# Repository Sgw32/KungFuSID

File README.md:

**Updater app is currently not working! Do not use it.**

# Kung Fu SID GD32 version

IMPORTANT! Firmware is adjusted for new Kung Fu SID hardware (and only)

## Introduction

Project is heavily inspired by __SwinSID__ and __ArmSID__ project. And is maintained as an open-source alternative to them.
Now it is even working on a GD32F405RGT6 on 168 MHz with 8 MHz crystal, just like Kung Fu Flash - and firmware is using critical code from KFF. 
I'm looking for contributers(I can even pay for the work) who will add some assembler optimization magic into SID code. 

A firmware for Kung Fu Flash and Kung Fu Flash GD32 which emulates SID via internal DAC of STM32F405RGT6
All hardware files are copied from "UltiSID" , projects are merged. 
Original UltiSID firmware is obsolete and current Kung Fu SID firmware just is partly based on it in IRQ and SID emulation. 

You can test Kung Fu SID by compiling firmware and flashing to your kung fu flash. 

To use it with original KungFuFlash cartridge output - check previous commits. 
Now only KungFuSID hardware is supported(and devices are selling)

Example usage with MixSIDs (you can use it directly, of course)

Patched by avrem for GD32F405RGT6 microcontroller.
Patch includes:
* ARR timer fix for GD32
* Memory remap fix (since KFF is running from RAM)

You can use both GD32 or STM32. 

## Future plans

I need to finish paddles, 6581-8580 switch and make a bootloader(optional, though). Probably, that's it and project will be finished. 
Some tunes still require some improvements, e.g. Artillery Credits by Geir Tjelta

## Limitations

* No 6581/8580 switch
* No paddles(can be done though)

## Video(and audio) 

## New video:

**PLEASE LIKE AND SUBSCRIBE😊**

Old video featuring old UltiSID firmware:

## Credits and special thanks:

* Tolaemon's NanoSwinSID page with open-hardware PCB available: http://www.tolaemon.com/nss/ 
My PCB is a modified version of SwinSID PCB

* ArmSID page with schematic: https://www.nobomi.cz/8bit/armsid/index_en.php
* Teensy SID emulator (huuuge, not really good): https://www.pjrc.com/c64-sid-chip-replacement/ and https://github.com/kokotisp/6581-SID-teensy
* SID BluePill emulators:
https://github.com/Bakisha/STM32-SID-PLAYER - my code is 80% based on this repository
https://github.com/dkm1978/BluePillSid - references
* Swinkels page - dead http://www.swinkels.tvtom.pl/swinsid/
Available on Archive.org - please check it, there is a SID emulation source for SwinSID atmega8515.
* Kung Fu Flash - https://github.com/KimJorgensen/KungFuFlash
I am inspired by simplicity of it and its power. 
* Pavel Myasnikov
Author of KungFuSID hardware design 
* Special greetings to Protovision Games

## Support us

Buy UltiSID here:
https://www.amibay.com/threads/kungfusid-sid-chip-emulator.2449119/

Crypto: 
0xeDc17cb23241eACe19DF3617291aa7d2d92E62DC (ETH, USDT ERC20)
Buy something here (3d models):
https://www.cgtrader.com/sgw32

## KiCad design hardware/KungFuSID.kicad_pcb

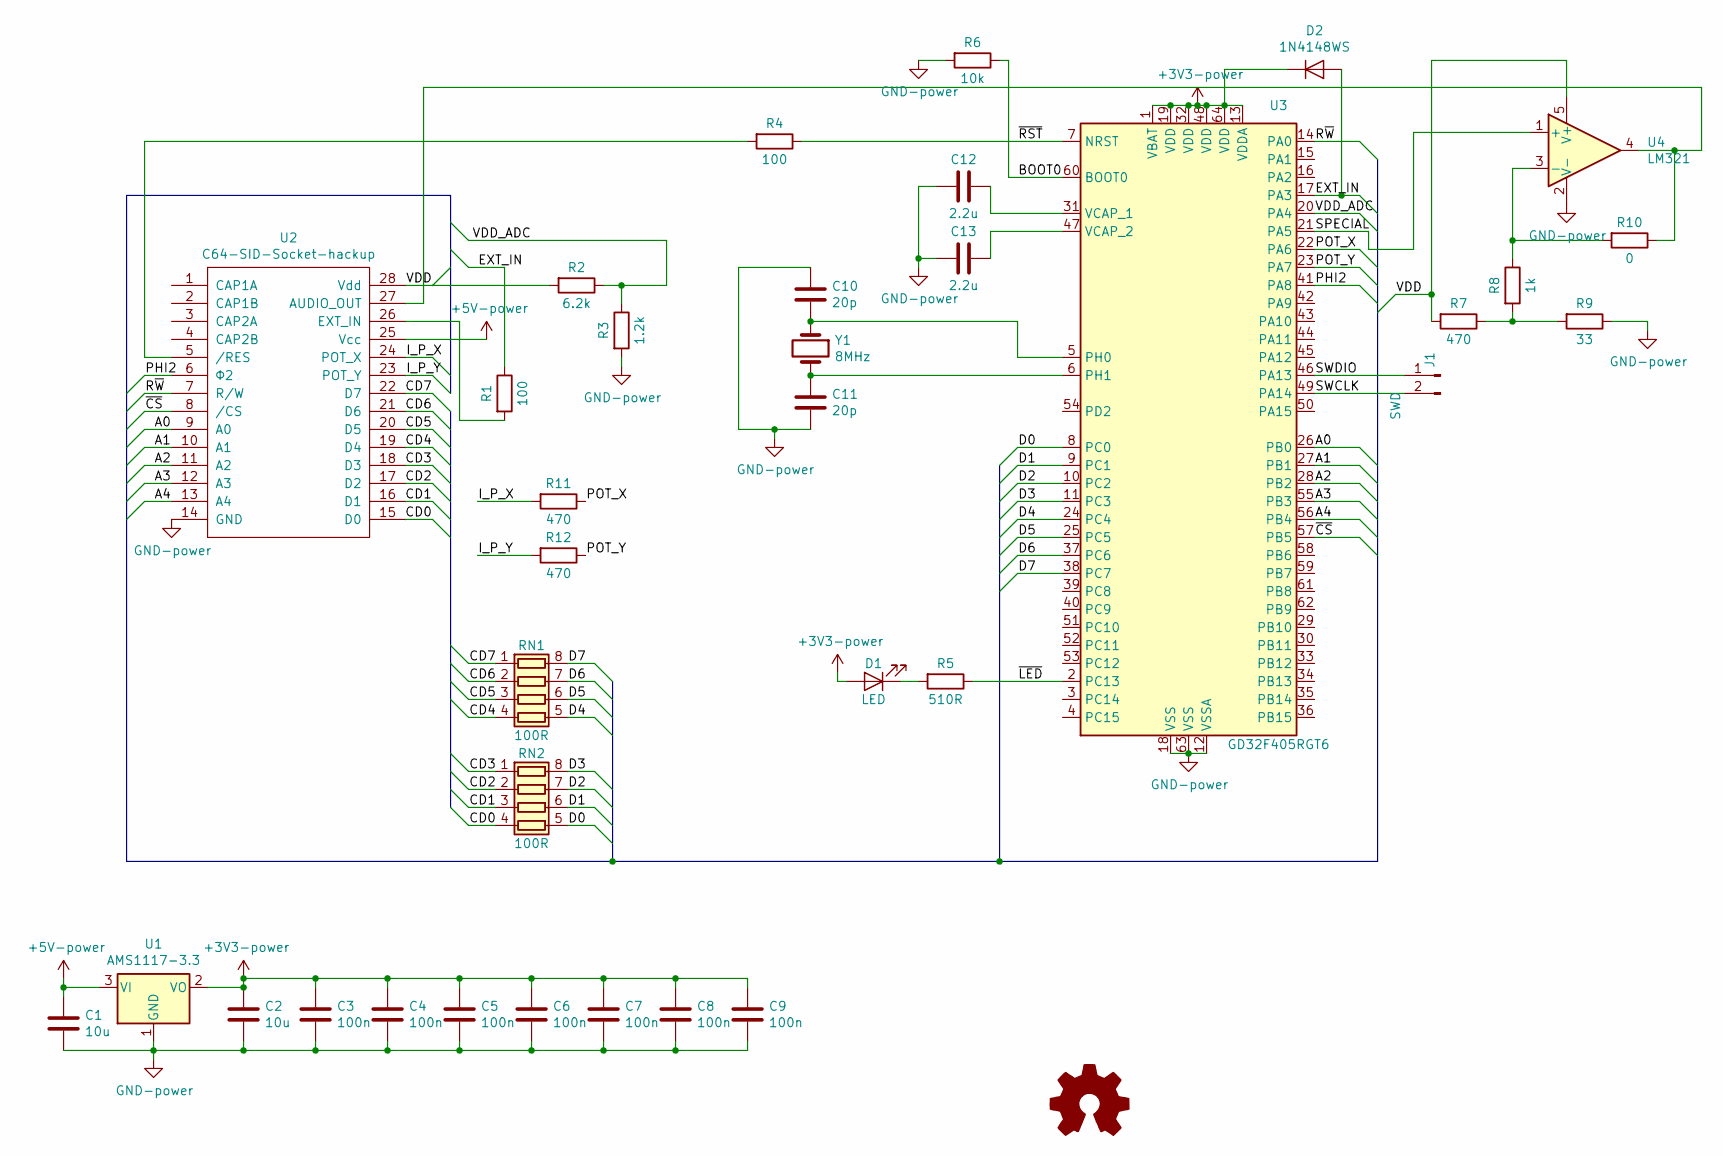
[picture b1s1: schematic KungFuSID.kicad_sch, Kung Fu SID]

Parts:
C1, C2: 10u; C_0402_1005Metric
C3, C4, C5, C6, C7, C8, C9: 100n; C_0402_1005Metric
C10, C11: 20p; C_0402_1005Metric
C12, C13: 2.2u; C_0402_1005Metric
D1: LED; LED_0402_1005Metric
D2: 1N4148WS; D_SOD-323
J1: SWD; PinHeader_1x02_P2.54mm_Vertical
R1, R4: 100; R_0402_1005Metric
R2: 6.2k; R_0402_1005Metric
R3: 1.2k; R_0402_1005Metric
R5: 510R; R_0402_1005Metric
R6: 10k; R_0402_1005Metric
R7, R11, R12: 470; R_0402_1005Metric
R8: 1k; R_0402_1005Metric
R9: 33; R_0402_1005Metric
R10: 0; R_0402_1005Metric
RN1, RN2: 100R; R_Array_Concave_4x0402
U1: AMS1117-3.3; SOT-89-3
U2: C64-SID-Socket-hackup; DIP-28_W15.24mm
U3: GD32F405RGT6; LQFP-64_10x10mm_P0.5mm
U4: LM321; SOT-23-5
Y1: 8MHz; Crystal_SMD_3225-2Pin_3.2x2.5mm

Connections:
+3V3: C2.1, C3.1, C4.1, C5.1, C6.1, C7.1, C8.1, C9.1, D1.2 (A), D2.1 (K), U1.2 (VO), U3.1 (VBAT), U3.13 (VDDA), U3.19 (VDD), U3.32 (VDD), U3.48 (VDD), U3.64 (VDD)
+5V: C1.1, U1.3 (VI), U2.25 (Vcc)
/A0: U2.9 (A0), U3.26 (PB0)
/A1: U2.10 (A1), U3.27 (PB1)
/A2: U2.11 (A2), U3.28 (PB2)
/A3: U2.12 (A3), U3.55 (PB3)
/A4: U2.13 (A4), U3.56 (PB4)
/BOOT0: R6.1, U3.60 (BOOT0)
/CD0: RN2.4 (R4.1), U2.15 (D0)
/CD1: RN2.3 (R3.1), U2.16 (D1)
/CD2: RN2.2 (R2.1), U2.17 (D2)
/CD3: RN2.1 (R1.1), U2.18 (D3)
/CD4: RN1.4 (R4.1), U2.19 (D4)
/CD5: RN1.3 (R3.1), U2.20 (D5)
/CD6: RN1.2 (R2.1), U2.21 (D6)
/CD7: RN1.1 (R1.1), U2.22 (D7)
/D0: RN2.5 (R4.2), U3.8 (PC0)
/D1: RN2.6 (R3.2), U3.9 (PC1)
/D2: RN2.7 (R2.2), U3.10 (PC2)
/D3: RN2.8 (R1.2), U3.11 (PC3)
/D4: RN1.5 (R4.2), U3.24 (PC4)
/D5: RN1.6 (R3.2), U3.25 (PC5)
/D6: RN1.7 (R2.2), U3.37 (PC6)
/D7: RN1.8 (R1.2), U3.38 (PC7)
/EXT_IN: D2.2 (A), R1.1, U3.17 (PA3)
/I_P_X: R11.2, U2.24 (POT_X)
/I_P_Y: R12.2, U2.23 (POT_Y)
/PHI2: U2.6 (Φ2), U3.41 (PA8)
/POT_X: R11.1, U3.22 (PA6)
/POT_Y: R12.1, U3.23 (PA7)
/R~W: U2.7 (R/W), U3.14 (PA0)
/SPECIAL: U3.21 (PA5), U4.1 (+)
/SWCLK: J1.2, U3.49 (PA14)
/SWDIO: J1.1, U3.46 (PA13)
/VDD: R2.2, R7.2, U2.28 (Vdd), U4.5 (V+)
/VDD_ADC: R2.1, R3.1, U3.20 (PA4)
/~CS: U2.8 (/CS), U3.57 (PB5)
/~LED: R5.1, U3.2 (PC13)
/~RST: R4.1, U3.7 (NRST)
GND: C1.2, C2.2, C3.2, C4.2, C5.2, C6.2, C7.2, C8.2, C9.2, C10.1, C11.2, C12.1, C13.2, R3.2, R6.2, R9.1, U1.1 (GND), U2.14 (GND), U3.12 (VSSA), U3.18 (VSS), U3.63 (VSS), U4.2 (V-)
unnamed: D1.1 (K), R5.2
unnamed: R7.1, R8.2, R9.2
unnamed: R10.1, U2.27 (AUDIO_OUT), U4.4
unnamed: R1.2, U2.26 (EXT_IN)
unnamed: R4.2, U2.5 (/RES)
unnamed: C10.2, U3.5 (PH0), Y1.1
unnamed: C11.1, U3.6 (PH1), Y1.2
unnamed: C12.2, U3.31 (VCAP_1)
unnamed: C13.1, U3.47 (VCAP_2)
unnamed: R8.1, R10.2, U4.3 (-)

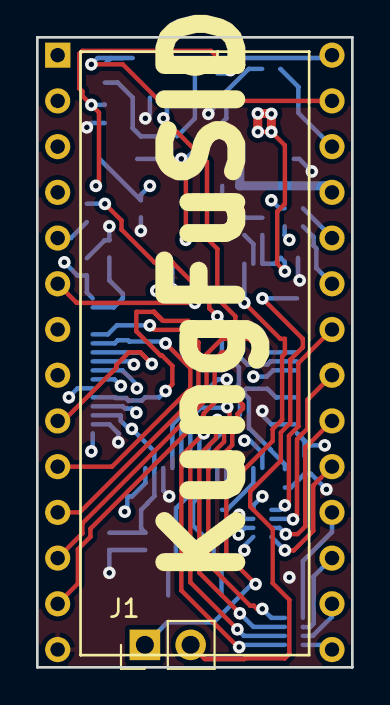
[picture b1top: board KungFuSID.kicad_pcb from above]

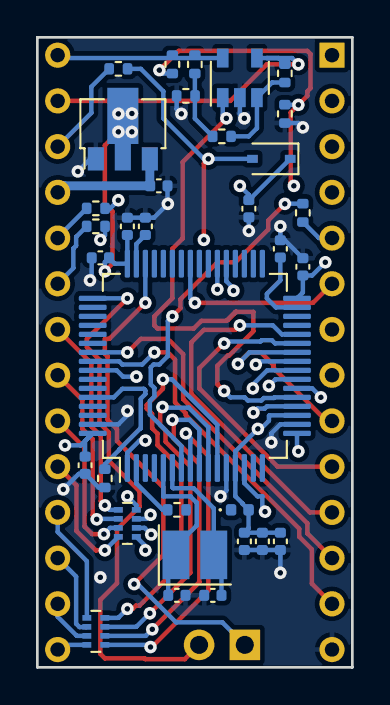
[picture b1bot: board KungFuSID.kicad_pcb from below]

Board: 4 copper layers, 17.5 x 35.0 mm, 35 parts (33 on the bottom side), 50 nets.

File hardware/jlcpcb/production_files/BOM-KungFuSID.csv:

Comment,Designator,Footprint,LCSC,Quantity
1.2k,R3,R_0402_1005Metric,C100219,1
6.2k,R2,R_0402_1005Metric,C100499,1
20p,"C10,C11",C_0402_1005Metric,C106203,2
10u,"C1,C2",C_0402_1005Metric,C15525,2
100n,"C3,C4,C5,C6,C7,C8,C9",C_0402_1005Metric,C159816,7
2.2u,"C12,C13",C_0402_1005Metric,C170151,2
1N4148WS,D2,D_SOD-323,C2128,1
100,"R1,R4",R_0402_1005Metric,C25138,2
470,R7,R_0402_1005Metric,C25167,1
510R,R5,R_0402_1005Metric,C25170,1
10k,R6,R_0402_1005Metric,C25531,1
1k,R8,R_0402_1005Metric,C25543,1
LED,D1,LED_0402_1005Metric,C434446,1
100R,"RN1,RN2",R_Array_Concave_4x0402,C48442,2
AMS1117-3.3,U1,SOT-89-3,C880752,1
8MHz,Y1,Crystal_SMD_3225-2Pin_3.2x2.5mm,C889706,1
LM321,U4,SOT-23-5,C9405,1
GD32F405RGT6,U3,LQFP-64_10x10mm_P0.5mm,C99031,1
C64-SID-Socket-hackup,U2,DIP-28_W15.24mm,,1
SWD,J1,PinHeader_1x02_P2.54mm_Vertical,,1
0,R10,R_0402_1005Metric,,1
33,R9,R_0402_1005Metric,,1
470,R11,R_0402_1005Metric,,1
470,R12,R_0402_1005Metric,,1
C64-SID-Socket-hackup,"U2_1,U2_2",DIP-28_W15.24mm,,2

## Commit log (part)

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2022-06-26 Set timer auto-reload
2022-07-09 Fix memory remap
2022-07-10 Change README.md
2023-02-28 Compiles but has a huge size
2023-03-19 First sound
2023-03-19 Slightly better
2023-03-19 Working
2023-05-03 Docs
2023-08-04 Small adjustments for new hardware
2023-08-04 Important!
2023-09-30 Small fixes
2023-10-03 Read from registers and OSC3 register $d41b (54299) works OK
2023-10-03 Frequency calibrated using Ode to Koto SID tune, using YouTube
2023-10-03 Remove old comments
2023-10-03 Nonworking optimized version
2023-10-03 many optimizations finished&working
2023-10-03 Some more opt
2023-10-03 Small opts
2023-10-03 Ringmod fixed
2023-10-03 Parametric timers
2023-10-03 Fix ADSR bug
2023-10-20 Revert back
2023-10-21 Add env from reSID. Currently not used
2023-10-21 Replaced buggy envelope processing using reSID project files
2023-10-28 Fix clamping
2023-11-28 Missing siddefs.h
2025-03-23 Hardware merge from UltiSID, update README.md
2025-03-23 Add pics
2025-03-23 Add CI Delete unused launcher Modify Makefile for correct name
2025-03-23 Modify CI, add badge
2025-03-23 Replace to unions, replace to uint32_t, add LUTs
2025-03-23 Bring back byte combination Delete multiplication in OSC
2025-03-25 Update LICENSE
2025-04-30 Revert some logic
2025-06-01 Attempts to make Potxy(please still use release version) Update of hardware files
2025-07-20 Optimize SID noise generation
2025-07-21 Hardcore optimize filter loop
2025-09-20 Optimize SID inner loops with inline assembly
2025-09-20 Optimize sync and ringmod handling in assembly
2026-01-09 Add firmware update register protocol
2026-01-12 Timing adjusted to fit MidiBox, less or no impact to sound quality
2026-01-14 Add updater (launcher from original Kung Fu Flash)
2026-01-14 Build updater as C64 PRG
2026-01-14 Updater test app
2026-01-14 Add release workflow and versioned artifacts
2026-01-17 Remove unused
2026-01-17 Move SID tick to PHI2 falling edge
2026-01-17 Add ADC-based SID model selection
2026-01-21 Clock TIM2 from PHI2 trigger
2026-02-23 Add C16 timing profile for DWT-based bus handlers
2026-02-24 Fix compilation
2026-02-24 Add comments with old C version
2026-02-24 Fix assembly
2026-02-24 Fix release pipeline
2026-02-24 Revise README
    Updated README to include updater app info
2026-02-24 Adjust timing to improve performance
2026-03-07 Add demo updater work in progress
2026-03-07 Exclude ADSR to another timer
2026-03-07 Updater works, adjust back the timings and irq
2026-03-07 Updater files and example .bin blob Use provided .bin only as example!
2026-03-14 Retry checksum reads three times in updaters
2026-03-14 add xparam reference
2026-03-14 Add EasyProg files from EasyFlash
2026-03-15 Add kfsid_prog updater flow and CI integration
2026-03-15 Implement xparam-based internal parameter storage and protocol module
2026-03-15 Remove EAPI/FAPI glue and rename easyprog to kfsidprog
2026-03-15 reduce mem
2026-03-15 Fix ld2.cfg main symbols for ld65 crt0 compatibility
2026-03-15 Adjust KFSID Prog appearance and make it running. Not tested on real hardware
2026-03-15 Simplify KFSID menu and remove EasyFlash flows
2026-03-15 Update workflow and example updater
